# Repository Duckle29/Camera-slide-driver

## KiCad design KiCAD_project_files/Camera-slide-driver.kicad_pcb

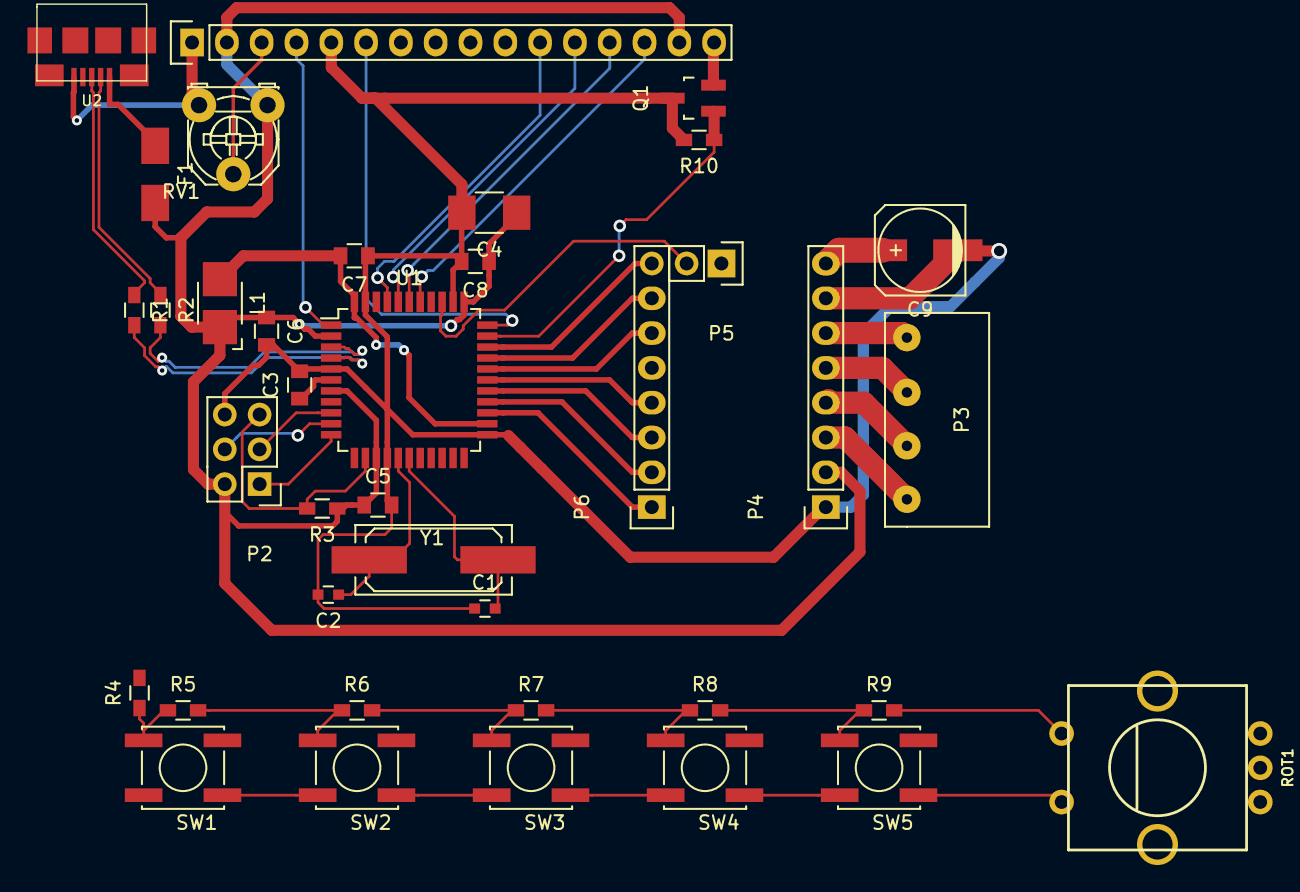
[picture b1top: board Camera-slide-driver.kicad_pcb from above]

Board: 2 copper layers, 38 parts (0 on the bottom side), 45 nets.

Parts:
C1, C2: 18pF; C_0603
C3: 1uF; C_0805
C4: 10uF; C_1210_HandSoldering
C5, C6, C7, C8: 100nF; C_0805
C9: 100uF; c_elec_6.3x7.7
DS1: LCD16X2; Socket_Strip_Straight_1x16
F1: F_Small; Fuse_SMD1206_HandSoldering
L1: 10uH; Inductor_1212
P2: CONN_02X03; Pin_Header_Straight_2x03
P3: CONN_01X04; JST_4_2mm_PTH
P4, P6: CONN_01X08; Socket_Strip_Straight_1x08
P5: CONN_01X02; Socket_Strip_Straight_1x02
Q1: Q_NMOS_GDS; SOT-23_Handsoldering
R1, R2: 22R; R_0603_HandSoldering
R3, R4, R8, R10: 10k; R_0603_HandSoldering
R5: 2k; R_0603_HandSoldering
R6: 3k; R_0603_HandSoldering
R7: 5k; R_0603_HandSoldering
R9: 30k; R_0603_HandSoldering
ROT1: ROTARY-ENCODER; SF-ROTARY-ENCODER
RV1: POT; Potentiometer_Triwood_RM-065
SW1, SW2, SW3, SW4, SW5: SW_PUSH; SW_SPST_EVPBF
U1: ATMEGA32U4-A; TQFP-44_10x10mm_Pitch0.8mm
U2: MICRO-B_USB
Y1: 16MHz; Q_49U3HMS

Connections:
+5V: C4.1, C5.1, C6.1, C8.1, DS1.2, DS1.15, F1.2, L1.1, P2.2, P4.2, R3.1, RV1.1, U1.2, U1.7, U1.14, U1.34
+24V: C9.1, P4.8
/STEP_M1A: P3.3, P4.4
/STEP_M1B: P3.4, P4.3
/STEP_M2A: P3.2, P4.5
/STEP_M2B: P3.1, P4.6
/USB_N: R2.2, U1.3
/USB_P: R1.2, U1.4
/UserInterface./0V: ROT1.1, ROT1.4, SW1.1, SW2.1, SW3.1, SW4.1, SW5.1
/UserInterface./Buttons: R9.2, ROT1.5
GND: C1.1, C2.2, C3.2, C4.2, C5.2, C6.2, C7.1, C8.2, C9.2, DS1.1, DS1.5, P2.6, P4.1, P4.7, Q1.3, R10.2, RV1.3, U1.5, U1.15, U1.23, U1.35, U1.43, U2.5
LCD_BL: Q1.1, R10.1, U1.32
LCD_D4: DS1.11, U1.41
LCD_D5: DS1.12, U1.40
LCD_D6: DS1.13, U1.39
LCD_D7: DS1.14, U1.38
LCD_E: DS1.6, U1.33
LCD_RS: DS1.4, U1.1
MISO: P2.1, U1.11
MOSI: P2.4, U1.10
unnamed: C1.2, U1.17, Y1.2
unnamed: C2.1, U1.16, Y1.1
unnamed: C3.1, U1.6
unnamed: C7.2, L1.2, U1.24, U1.44
unnamed: DS1.3, RV1.2
unnamed: DS1.16, Q1.2
unnamed: F1.1, U2.1
unnamed: R4.1, R5.1, SW1.2
unnamed: R5.2, R6.1, SW2.2
unnamed: R6.2, R7.1, SW3.2
unnamed: R7.2, R8.1, SW4.2
unnamed: R8.2, R9.1, SW5.2
RESERVED: U1.20, U1.21
RST: P2.5, R3.2, U1.13
SCK: P2.3, U1.9
STEP_CFG1: P6.7, U1.30
STEP_CFG2: P6.6, U1.29
STEP_DIR: P6.1, U1.25
STEP_EN: P6.8, U1.31
STEP_NC0: P6.3, U1.27
STEP_NC1: P6.4, U1.28
STEP_STEP: P6.2, U1.26
STEP_VREF: P5.2, U1.36
USB_D+: R1.1, U2.3
USB_D-: R2.1, U2.2

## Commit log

2015-12-20 Initial commit and push
2015-12-20 added PDF
